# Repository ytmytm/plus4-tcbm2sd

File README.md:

# TCBM2SD 
---------
### by Maciej 'YTM/Elysium' Witkowiak

CBM 1551 paddle replacement and/or mass storage using an SD card interfacing with the Commodore C16/116/Plus4 simulating a TCBM bus 1551 disk drive.

## Ecosystem

This board can also serve as the Commodore-side TCBM interface for the [Pi1551](https://github.com/ytmytm/Pi1551), a cycle-exact Commodore 1551 emulator for Raspberry Pi. It can be used with either the [Pi1551-HAT](https://github.com/ytmytm/PI1551-hat) or [Pi1551-III](https://github.com/ytmytm/PI1551-III) interface.

It is also the TCBM interface for the [1551-rePico](https://github.com/ytmytm/1551-rePico), a 1551 drive replacement that uses a real 6510T with Raspberry Pico 2 emulating the analog parts.

The [Parobek function ROM](https://github.com/ytmytm/plus4-parobek) is a useful way to populate the 32/64 KiB ROM socket. It includes the TCBM2SD boot software, so `boot.t2sd` is not needed when using that ROM.

## Detailed manuals

- [User's manual](UserManual.md)
- [Hardware assembly, firmware compilation and flashing](HardwareFirmware.md)

## Software

- Supported by [Siz's I/O library v4](https://github.com/iszell/siziolib)
- [GEOS for tcbm2sd (D64)](geos/geostcbm.d64)
- [Collection of patched disk games](games/)
- [Parobek function ROM](https://github.com/ytmytm/plus4-parobek)
<!-- XXX patched cartridge images: OctaBASIC, Gamecart -->

[ZIP archive of the above](https://drive.google.com/drive/folders/1UYzHO3PNRJw3JCk5QNncfK0rwXZ2pFXH?usp=drive_link)

## Media

### Commodore Users Europe presentation

<a href="https://www.youtube.com/watch?v=iNGW5h6bXoA" target="_blank">
 
 <p><small>Click for video</small></p>
</a>

### Photos

*The photos and PCB view below show an older board revision and are provided for reference only.*

### Basic operations

<a href="https://www.youtube.com/watch?v=6DOctO64GS4" target="_blank">
 
 <p><small>Click for video</small></p>
</a>

### Fastloader

<a href="https://www.youtube.com/watch?v=Cf42Z9H2JiA" target="_blank">
 
 <p><small>Click for video</small></p>
</a>

## Features

### Drive simulator

TCBM2SD does not emulate a 1551, but simulates its behavior:

- DLOAD and DSAVE support for files
- read-only support for disk images (D64, D71, D81, D80, D82) as subdirectories
- standard Kernal transfer at about 3100 b/s (a little less than JiffyDOS 1541, and about twice as fast as a 1551 at 1600 b/s); fastload at about 9300 b/s (**23×** as fast as a 1541, about **6×** as fast as a 1551), with [patched Directory Browser v1.2](loader/); on par with DolphinDOS
- fastload booter embedded in the flash, available as the `*` file, which loads and runs `BOOT.T2SD` from the root directory; this can be any file that runs from BASIC. [Directory Browser patched with fastload protocol](loader/db12b.prg) is recommended. When using the Parobek function ROM, `BOOT.T2SD` is already included in the ROM and is not needed on the SD card.
- CBM DOS disk commands: `CD`, `R`, `S`, `MD`, `RD`, `I`, `UI`, `UJ`
- utility commands similar to 1571/81 BURST for fastloader, block-read/write and device number change
- device number stored permanently in EEPROM or configurable with jumpers
- support for absolute paths (up to 71 characters)
- support for SD change detection (if the SD card socket supports it) to automatically initialize card
- PREV/NEXT buttons to switch between disk images
- socket for a 32/64 KiB cartridge ROM

### Paddle replacement

It has been confirmed that tcbm2sd works as a 1551 paddle cartridge replacement with a real 1551 drive. The Arduino can be removed or disabled for this purpose.

- PLA 251641-3 and 6523T (28 pin triport) integrated into a single CPLD
- low part count: CPLD, 3.3V voltage regulator and four capacitors
- only 8 I/O addresses are needed for I/O, but certain fastloaders require the mirrored registers to be present, so we keep using whole 32-byte space like the original PLA:
  - FEE0-FEFF (instead of FEF0-FEF7) for device 8
  - FEC0-FEDF (instead of FEC0-FEC7) for device 9

### Platform for TCBM developments

The paddle part exposes all TCBM bus signals and can be used as a basis for other TCBM hardware projects.

For development, another daughterboard or a ready-to-use microcontroller module can be used. All TCBM bus signals are exposed at the cartridge edge (TCBM connector) or Arduino footprint. Signals are already at 3.3 V logic, so no additional level shifter is necessary for a Raspberry Pi.

*Please note that if a TCBM cable is connected then both pins 1 and 16 of the TCBM connection must be connected to GND. It's used by Arduino to detect if TCBM cable is attached so that Arduino can disable itself.*

### Availability

The information published here includes everything required to manufacture the PCB (Gerber files) and program the firmware.

If you want a completed unit, please drop me a message (you will find my email address at the top of [loader/loader.asm](loader/loader.asm)). I might have some units to sell; please include your country.

<!--
You can also order the hardware from PCBWay. This is the PCB only; it still requires programming the CPLD and soldering the Arduino Pro Mini (or TCBM connector) and voltage regulator:

  -->

## Case

You might also be interested in a cartridge case. It should [fit inside this one](https://www.thingiverse.com/thing:6309306), although it requires cutting a slot for the SD card.

*This example shows revision 1.1 without NEXT/PREV buttons*

There is also an [updated case project](https://www.thingiverse.com/thing:7314711) that should fit revision 1.3 and 1.4 PCBs without any extra holes.

## Credits

This project builds on work and documentation provided by others:

- [Fake6523](https://github.com/go4retro/Fake6523) and [Fake6523 HW](https://github.com/ZXByteman/Fake6523), which provided the basis for the trimmed-down 6523T implementation
- [cia-verilog](https://github.com/niklasekstrom/cia-verilog/blob/master/cia.v) which showed me a better way of interfacing with CPU bus
- [Commodore TCBM bus and protocol description](https://www.pagetable.com/?p=1324)
- [c264-magic-cart](https://github.com/msolajic/c264-magic-cart) and [C264Cart](https://github.com/hackup/C264Cart) which were my template for PCB dimensions
- [LittleSixteen](https://github.com/SukkoPera/LittleSixteen) where I found KiCad expansion port footprint and symbol, also helped me to understand how Plus/4 expansion port works
- [kicad-lib-arduino](https://github.com/g200kg/kicad-lib-arduino)
- @eper973 for Directory Browser source code
- Per Olofsson for `diskimage.c` D64/71/81 handling code

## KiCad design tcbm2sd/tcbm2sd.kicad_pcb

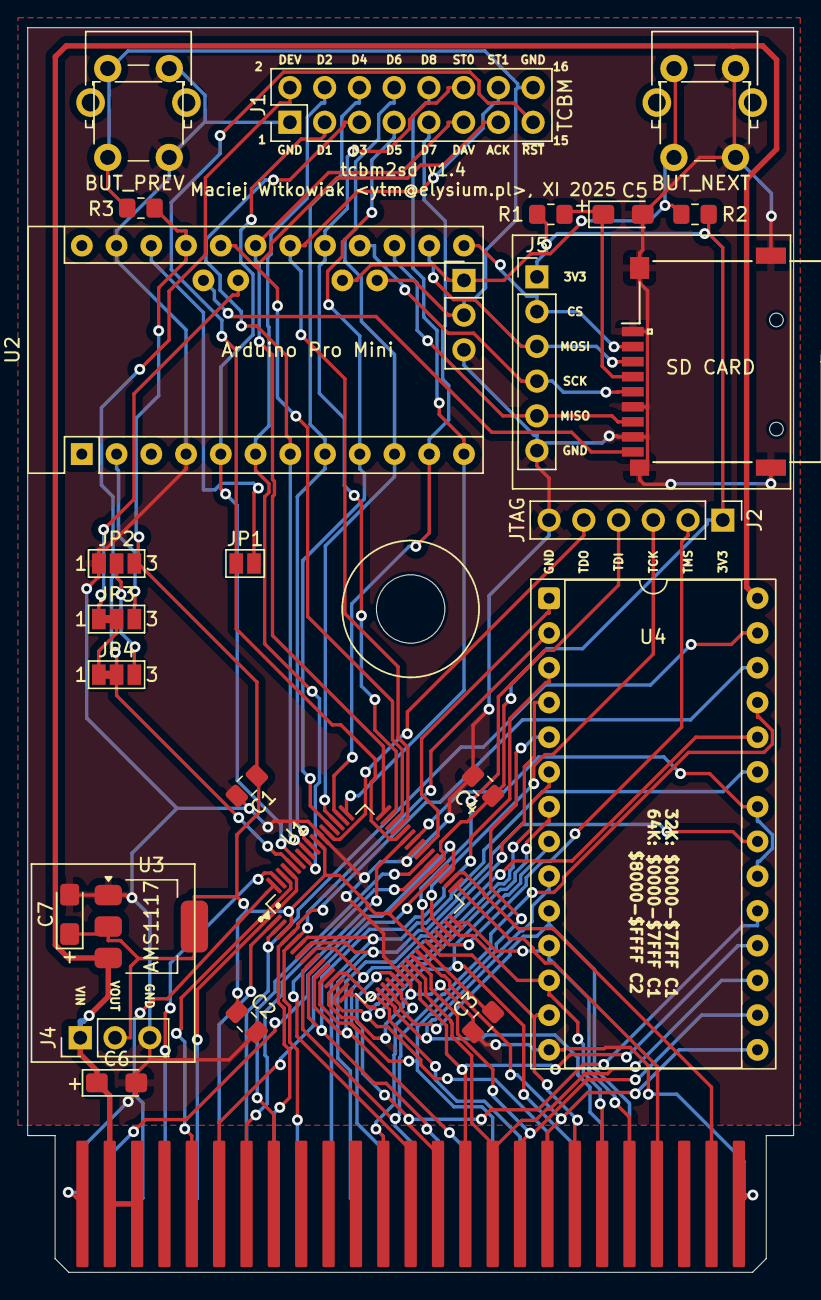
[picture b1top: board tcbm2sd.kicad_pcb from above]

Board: 2 copper layers, 56.0 x 91.0 mm, 27 parts (0 on the bottom side), 72 nets.

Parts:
C1, C2, C3, C4: 0.1uF; C_0805_2012Metric_Pad1.18x1.45mm_HandSolder
C5, C6, C7: 10µ; CP_EIA-3216-12_Kemet-S_HandSolder
J1: TCBM; PinHeader_2x08_P2.54mm_Vertical
J2: JTAG; PinHeader_1x06_P2.54mm_Vertical
J4: AMS1117; PinHeader_1x03_P2.54mm_Vertical
J5: SD CARD; PinHeader_1x06_P2.54mm_Vertical
J7: ALT_A6_A7; PinHeader_1x03_P2.54mm_Vertical
JP1: SolderJumper_2_Open; SolderJumper-2_P1.3mm_Open_Pad1.0x1.5mm
JP2: SolderJumper_3_Open; SolderJumper-3_P1.3mm_Open_Pad1.0x1.5mm_NumberLabels
JP3, JP4: SolderJumper_3_Bridged12; SolderJumper-3_P1.3mm_Bridged12_Pad1.0x1.5mm_NumberLabels
R1: 2.2R; R_0805_2012Metric_Pad1.20x1.40mm_HandSolder
R2, R3: 10K; R_0805_2012Metric_Pad1.20x1.40mm_HandSolder
SW1: BUT_PREV; SW_PUSH_6mm_OR_SW_Tactile_SPST_Angled_PTS645Vx58-2LFS
SW2: BUT_NEXT; SW_PUSH_6mm_OR_SW_Tactile_SPST_Angled_PTS645Vx58-2LFS
U1: XC9572XL-VQ64; TQFP-64_10x10mm_P0.5mm
U2: Arduino Pro Mini; Arduino_Pro_Mini
U3: AMS1117-3.3; SOT-223-3_TabPin2
U4: 27C512; DIP-28_W15.24mm_Socket
U$1: C16_CARTRIDGE; C16_CART
XS1: SD connector; Conn_uSDcard

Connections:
+3V3: C1.1, C2.1, C3.1, C4.1, C7.1, J2.1, J4.2, J5.1, JP2.3 (B), R1.2, R2.1, R3.1, U1.3 (VCC), U1.26 (VCCIO), U1.37 (VCC), U1.55 (VCCIO), U2.21 (VCC), U3.2 (VO)
/A0: U1.18, U4.10 (A0), U$1.Y (A0)
/A1: U1.17 (I/O/GCK3), U4.9 (A1), U$1.X (A1)
/A2: U1.16 (I/O/GCK2), U4.8 (A2), U$1.W (A2)
/A3: U1.15 (I/O/GCK1), U4.7 (A3), U$1.V (A3)
/A4: U1.13, U4.6 (A4), U$1.U (A4)
/A5: U1.12, U4.5 (A5), U$1.T (A5)
/A6: U1.11, U4.4 (A6), U$1.S (A6)
/A7: U1.10, U4.3 (A7), U$1.R (A7)
/A8: U1.9, U4.25 (A8), U$1.P (A8)
/A9: U1.8, U4.24 (A9), U$1.N (A9)
/A10: U1.7, U4.21 (A10), U$1.M (A10)
/A11: U1.6, U4.23 (A11), U$1.L (A11)
/A12: U1.5 (I/O/GTS1), U4.2 (A12), U$1.K (A12)
/A13: U1.4, U4.26 (A13), U$1.J (A13)
/A14: U1.2 (I/O/GTS2), U4.27 (A14), U$1.H (A14)
/A15: U1.1, U$1.F (A15)
/ACK: J1.13, U1.46, U2.20 (D17/A3)
/AEC: U1.33, U$1.22 (AEC)
/ALT_A6: J1.16, J7.2, R3.2, SW1.1, U2.A6
/ALT_A7: J7.1, R2.2, SW2.1, U2.A7
/BA: U1.43, U$1.13 (BA)
/C1HI: U1.36, U$1.6 (C1HI)
/C1LO: U1.35, U$1.B (C1LO)
/C2HI: U1.39, U$1.8 (C2HI)
/C2LO: U1.38, U$1.7 (C2LO)
/D0: U1.32, U4.11 (D0), U$1.21 (D0)
/D1: U1.31, U4.12 (D1), U$1.20 (D1)
/D2: U1.27, U4.13 (D2), U$1.19 (D2)
/D3: U1.25, U4.15 (D3), U$1.18 (D3)
/D4: U1.24, U4.16 (D4), U$1.17 (D4)
/D5: U1.23, U4.17 (D5), U$1.16 (D5)
/D6: U1.22, U4.18 (D6), U$1.15 (D6)
/D7: U1.20, U4.19 (D7), U$1.14 (D7)
/DAV: J1.11, U1.48, U2.19 (D16/A2)
/DEV: J1.2, JP4.2 (C), U1.60
/DIO1: J1.3, U1.59, U2.5 (D2)
/DIO2: J1.4, U1.58, U2.6 (~D3)
/DIO3: J1.5, U1.57, U2.7 (D4)
/DIO4: J1.6, U1.56, U2.8 (~D5)
/DIO5: J1.7, U1.52, U2.9 (~D6)
/DIO6: J1.8, U1.51, U2.10 (D7)
/DIO7: J1.9, U1.50, U2.11 (D8)
/DIO8: J1.10, U1.49, U2.12 (~D9)
/MUX: U1.19, U$1.12 (MUX)
/PHI0: U1.61, U$1.E (PHI0)
/PHI2: U1.34, U$1.24 (PHI2)
/ROM_A15: U1.40, U4.1 (A15)
/R/~W: U1.62, U$1.5 (R/~W)
/SD_CD: U2.A5, XS1.9 (CD)
/SD_CS: J5.2, U2.13 (~D10), XS1.2 (CS/DAT3)
/SD_MISO: J5.5, U2.15 (D12), XS1.7 (DO/DAT0)
/SD_MOSI: J5.3, U2.14 (~D11), XS1.3 (DI/CMD)
/SD_SCK: J5.4, U2.16 (D13), XS1.5 (CLK)
/STATUS0: J1.12, U1.47, U2.17 (D14/A0)
/STATUS1: J1.14, U1.45, U2.18 (D15/A1)
/TCK: J2.3, U1.30 (TCK)
/TDI: J2.4, U1.28 (TDI)
/TDO: J2.5, U1.53 (TDO)
/TMS: J2.2, U1.29 (TMS)
/VCC: C6.1, J4.1, U3.3 (VI), U4.28 (VCC), U$1.2 (5V), U$1.3 (5V)
/~RAS: U1.63, U$1.D (~RAS)
/~RESET_3_3V: J1.15, JP1.1 (A), U1.44
/~RESET: U1.64 (I/O/GSR), U$1.C (~RESET)
/~ROMCS: U1.42, U4.20 (~CE), U4.22 (~OE)
GND: C1.2, C2.2, C3.2, C4.2, C5.2, C6.2, C7.2, J1.1, J2.6, J4.3, J5.6, J7.3, JP2.1 (A), SW1.2, SW2.2, U1.14 (GND), U1.21 (GND), U1.41 (GND), U1.54 (GND), U2.4 (GND), U2.23 (GND), U3.1 (GND), U4.14 (GND), U$1.1 (GND), U$1.25 (GND), U$1.A (GND), U$1.CC (GND), XS1.1 (DAT2), XS1.6 (GND), XS1.8 (DAT1)
unnamed: JP1.2 (B), U2.22 (RST)
unnamed: JP2.2 (C), JP4.3 (B)
unnamed: JP3.1 (A), U2.A4
unnamed: JP3.3 (B), U2.2 (D0/RX)
unnamed: JP3.2 (C), JP4.1 (A)
unnamed: C5.1, R1.1, XS1.4 (Vdd)

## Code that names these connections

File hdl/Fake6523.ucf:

# Fake6523A-28
NET "_reset"		LOC = "P64"  ; # /RESET exp. C
NET "_write"		LOC = "P62"  ; # R/W exp. 5
NET "data<0>"		LOC = "P32"  ; # D0 exp. 21
NET "data<1>"		LOC = "P31"  ; # D1 exp. 20
NET "data<2>"		LOC = "P27"  ; # D2 exp. 19
NET "data<3>"		LOC = "P25"  ; # D3 exp. 18
NET "data<4>"		LOC = "P24"  ; # D4 exp. 17
NET "data<5>"		LOC = "P23"  ; # D5 exp. 16
NET "data<6>"		LOC = "P22"  ; # D6 exp. 15
NET "data<7>"		LOC = "P20"  ; # D7 exp. 14
NET "port_a<0>"	LOC = "P59"  ; # DIO1, <-> wire 3
NET "port_a<1>"	LOC = "P58"  ; # DIO2, <-> wire 4
NET "port_a<2>"	LOC = "P57"  ; # DIO3, <-> wire 5
NET "port_a<3>"	LOC = "P56"  ; # DIO4, <-> wire 6
NET "port_a<4>"	LOC = "P52"  ; # DIO5, <-> wire 7
NET "port_a<5>"	LOC = "P51"  ; # DIO6, <-> wire 8
NET "port_a<6>"	LOC = "P50"  ; # DIO7, <-> wire 9
NET "port_a<7>"	LOC = "P49"  ; # DIO8, <-> wire 10
NET "port_b<0>"	LOC = "P47"  ; # STATUS0, <-, wire 12
NET "port_b<1>"	LOC = "P45"  ; # STATUS1, <-, wire 14
NET "port_c<6>"	LOC = "P46"  ; # ACK, ->, wire 13 (controller's ACK out, drive's DAV in)
NET "port_c<7>"	LOC = "P48"  ; # DAV, <-, wire 11 (controller's DAV in,  drive's ACK out)
NET "rs<0>"			LOC = "P18"  ; # A0 exp. Y
NET "rs<1>"			LOC = "P17"  ; # A1 exp. X
NET "rs<2>"			LOC = "P16"  ; # A2 exp. W
# /CS from PLA (18) F0

# PLA outputs
#NET "_cs"			LOC = "P34"  ;	# PLA F0 (18) -> 6523 /CS (12)
#NET "pla_f7" 		LOC = "P33"  ; # PLA F7 (10) -> I0 (2)
NET "phi2"			LOC = "P34"  ;	# Phi2 exp. 24
NET "aec" 		LOC = "P33"  ; # AEC exp. 22
NET "_cas"		LOC = "P42"  ; # /CAS exp. 11
NET "ba"		LOC = "P43"  ; # BA exp. 13
# PLA inputs
# PLA I0 (9) <- PLA F7 (10) (wired back)
NET "pla_i<1>"		LOC = "P6"	 ; # PLA I1 (8)   <- A11 exp. L
NET "pla_i<2>"		LOC = "P5"	 ; # PLA I2 (7)   <- A12 exp. K
NET "pla_i<3>"    LOC = "P4"	 ; # PLA I3 (6)   <- A13 exp. J
NET "pla_i<4>"		LOC = "P2"	 ; # PLA I4 (5)   <- A14 exp. H
NET "pla_i<5>"		LOC = "P1"	 ; # PLA I5 (4)   <- A15 exp. F
NET "pla_i<6>"		LOC = "P61"  ; # PLA I6 (3)   <- Phi0 exp. E
NET "pla_i<7>"		LOC = "P63"	 ; # PLA I7 (2)   <- /RAS exp. D
NET "pla_i<8>"		LOC = "P60"  ; # PLA I8 (27)  <- DEV signal from device (0 or 1), wire 2
NET "pla_i<9>"    LOC = "P7"   ; # PLA I9 (26)  <- A10 exp. M
NET "pla_i<10>"   LOC = "P19"  ; # PLA I10 (25) <- MUX exp. 12
NET "pla_i<11>"   LOC = "P8"   ; # PLA I11 (24) <- A9 exp. N
NET "pla_i<12>"   LOC = "P9"   ; # PLA I12 (23) <- A8 exp. P
NET "pla_i<13>"   LOC = "P10"  ; # PLA I13 (22) <- A7 exp. R
NET "pla_i<14>"   LOC = "P11"  ; # PLA I14 (21) <- A6 exp. S
NET "pla_i<15>"   LOC = "P12"  ; # PLA I15 (20) <- A5 exp. T
# additional inputs
NET "addr<4>"     LOC = "P13"  ; # PLA xxx      <- A4 exp. U
NET "addr<3>"     LOC = "P15"  ; # PLA xxx      <- A3 exp. V
# additional output
NET "_resetout"   LOC = "P44"  ; # copy 5V /RESET to 3.3V /RESET

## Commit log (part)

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2024-07-05 handle file saving to SD card
2024-07-05 dummy directory load
2024-07-05 remark about file pattern matching
2024-07-06 real directory listing
2024-07-06 keep current path in 'pwd' string (must end with '/')
2024-07-06 improve drive status message handling
2024-07-06 keep SD code enabled at all times now
2024-07-06 in blocking read command function wait only for a valid command
2024-07-07 add volatile inline clauses to all low level h/w functions
2024-07-07 disable debug
2024-07-07 show current directory name as volume label
2024-07-07 some programs will expect that command is executed right after UNLISTEN, not after following CLOSE (which may not come at all - Directory Browser)
2024-07-07 try to handle transfer problems within filebrowser/directory browser with a tiny delay (but port_read_slow is very slow)
2024-07-08 logic with feedback, seems to fix hangup problems
2024-07-08 clarify DAV/ACK confusion
2024-07-08 correct TCBM 0/1 IEC 8/9 numbering info (A5==1 is for device 8)
2024-07-08 comments
2024-07-08 updated logic: use A4/A3 to decode addresses, no more glitches, copy /RESET in 3.3V to pin 44
2024-07-08 updated after latest runs
2024-07-08 DEV must be an output, it can't be an input from CPLD because Arduino won't have time to react (it would come from A4/A5 address lines)
2024-07-09 remove dead code
2024-07-09 convert everything to lowercase PETSCII (uppercase ASCII)
2024-07-09 don't prepend with current dir (pwd) if filename starts with '/'
2024-07-09 move state_init to reset input buffer
2024-07-09 be sure to close opened files
2024-07-09 credits
2024-07-09 return so that valid U0>x results in OK status
2024-07-09 fix comments about pin definitions
2024-07-10 remove delay, it's no longer necessary
2024-07-10 use plain ASCII for directory listing (same as with filename matching)
2024-07-10 put all Serial debug messages within 'if debug {}'; gcc optimizes this away and it's cleaner than #ifdef DEBUG
2024-07-10 PCB top view
2024-07-10 added README placeholder
2024-07-12 directory browser v1.2 patched for fastloader; first with loader part disassembled no changes yet; this is binary identical
2024-07-12 gitignore
2024-07-12 comments and assert
2024-07-13 WIP fastload protocol and directory browser patch
2024-07-14 when asked for '*' load embedded Directory Browser 1.2 (works with shift+run/stop)
2024-07-14 disable browser when debug is enabled (would not fit in flash)
2024-07-14 do nothing with empty command
2024-07-14 support for rename command
2024-07-14 document new disk commands
2024-07-15 extra documentation
2024-07-17 diary added
2024-07-21 comments and indentation
2024-07-21 it's more readable to send out whole strings
2024-07-21 report 9999 blocks free (no need for a real value)
2024-07-21 missing cases for STATE_BROWSER (STATE_STAT and STATE_BROWSER are handled in the same way)
2024-07-21 correct comment
2024-07-21 fastload protocol for directory with test program
2024-07-21 SHIFT+RUN/STOP to load tiny loader that will find and load 'BOOT.T2SD' with fastload protocol
2024-07-21 increase name buffer size to 256 bytes as dictated by SdFat
2024-07-21 if filename is longer than 16 characters, fall back on 8.3 short DOS filename
2024-07-21 map 0x7e ~ (short filename marker) to 0x5e <- and back, because otherwise it came out as (pi) and short filename couldn't be found
2024-07-21 reformat and indents
2024-07-21 reset if BOOT.T2SD file not found
2024-07-21 correct DISABLE_BROWSER option (not relevant anymore)
2024-07-23 clean pcb, new revision
2024-07-23 - solder jumpers to choose DEV from +33V/GND/A4/D1 - TCBM connector - removed debug pads - RESET 3.3V, through solder jumper - cut connection to Arduino pin 3 (RP2040 clone has GND there) - VCC net c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
2024-07-24 new plots: schematic and gerber files
2024-07-24 jlcpcb manufacturing files: BOM and placement (corrected U1 rotation from 45 to -45)
2024-07-24 updated snapshot
2024-07-24 correctly skip partition number (skip '0' only if the next character is ':')
2024-07-24 #define for maximum size of file's long name
2024-07-24 remove all arduino strings
2024-07-25 diskimage 0.95 library converted to readonly+SdFat interface ; http://web.archive.org/web/20240330040552/https://www.paradroid.net/diskimage/
2024-07-25 enter/exit disk images; list disk image contents
2024-07-25 put filetype strings in flash
2024-07-25 reuse input_buf for temporary storage for directory file entry buffer
2024-07-25 reduce input/output buffer size
2024-07-25 cleanup compiler warnings
2024-07-25 bump minor version by 1 because we support disk images now
2024-07-25 update on RAM situation: needs about 600 free bytes left for dynamic stuff, PATH_SIZE is used twice, use 24 for debug, safe max is about 72 now
2024-07-26 reset status to 00 (b/c output_buf is altered by match_filename)
2024-07-27 directory browser 1.2 (tcbm) binary and code samples
2024-07-27 recognize D71/81 with error info and D64 with 40 and 42 tracks (read only, BAM not correctly handled for 40/42 even for free blocks)
2024-07-27 correct directory search for D81
2024-07-27 case info
2024-07-27 dimensions
2024-08-04 fix compiler warning
2024-08-15 updated to rev1.1
2024-08-18 make all unused port bits hi-z
2024-08-25 drop PLA outputs, use more exp. port inputs to CPLD (just in case) own SMD 3.3V regulator circuit own SD card circuit (SD card model etc.) from SD2IEC plug https://www.hackup.net/2018/10/sd2iecplug-v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
2024-08-30 add 32/64K EEPROM with /CS done using two diodes with pullup as AND one more pullup for A15 line connector for remaining Arduino lines with GND connection to short it to disable Arduino on boot
2024-09-03 twin dip/soic footprints (won't use them)
2024-09-03 production files
2024-09-04 cleanup pins, pla_f7/_cs debug outputs back - to gpio pins
2024-09-07 enable pullups on DIO1-8
2024-09-07 disable Arduino if BUT_PREV is tied to GND
2024-09-07 load and save on any channel except 15
2024-09-11 alternative A7 pullup, but disabling function disabled for now
2024-09-12 A6/A7 are analog-only, can't use as digital inputs
2024-09-14 simplified design that actually works on both 7501 and 6510
2024-09-14 back up Fake6523 name
2024-09-14 diary
2024-09-14 urls for reference
2024-09-15 save one byte
2024-09-15 call CLOSE after CLKCHN so that UNTALK is properly sent
2024-09-15 use Kernal jumptable for function calls; call UNTALK at the end (not required)
2024-09-15 if in image, then '*' loads first file, not browser booter
2024-09-15 handle special case for directory listing with JiffyDOS @$ - calls UNTALK/TALK/TKSA after each received line
2024-09-15 handle PREV/NEXT buttons; a bit clumsy because we need to scan directory each time
2024-09-16 A6/A7 might not be connected (pulled up) at all, check that by probing A7 first - if it's not pulled up we can't use these buttons (or TCBM cable sense) at all
2024-09-16 standardload / fastload refactor - merge procedures into one to save flash space
2024-09-16 restore analog threshold
2024-09-16 reduce debouncing delay for prev/next buttons
2024-09-16 if going to previous image of the first image or next image of the last image - stay on the current image
2024-09-16 if SD card was changed close the image, but also go to root folder (reload_sd_card() won't do that because it's called by I/UI/UJ commands)
2024-09-17 smaller simpler loader with quasi-BURST CMD TEN command (fastload utility); bump version to indicate utility U0 commands are present https://www.devili.iki.fi/Computers/Commodore/C1571/firmware/fastu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
2024-09-17 utility command U0<$3F><track><sector> to load file from disk image by its first block's t&s
2024-09-18 public function to compute offset to given track&sector within the image file
2024-09-18 now we support block-write, so disk image has to be opened in O_RDWR mode
2024-09-18 block-read/write utility commands and new state data streaming function
2024-09-18 simple example about utility commands for block-read/write
2024-09-18 update about block-read/write
2024-09-19 save one RAM byte, global cbm_errno is not used
2024-09-19 docs update
2024-09-19 corrected
2024-09-25 less verbose debug2
2024-09-25 no need to wait for anything with fastprotocol - the last byte was already confirmed, just cleanup
2024-09-25 GEOS support
2024-09-26 add debug2 or debug2>1 to more cases
2024-09-26 correct finish of fast block read/write
2024-09-26 clean bootdisk, without TDISK 1551 drive code file, to have 3 more free blocks
2024-09-28 cleanup and credits
2024-09-29 copy only low level from /RESET line, keep /RESET_3_3V high impedance otherwise
2024-10-01 handle ROM in CPLD; temporarily disable resetout and reuse it for rom_cs (in the next rev. use loc P42 instead and bring back resetout)
2024-10-01 remove GPIO connector, 74'00, diodes and pullup; added pullups for A6/A7; JP1 (reset passthrough) default open; bump revision to 1.3
2024-10-04 updated routing
2024-10-06 dual footprint for pushbutton switch straight or angled
2024-10-09 confirmed working on my C16
2024-10-13 option to disable A6/A7 buttons for v1.0/v1.1 PCBs
2024-10-17 scan 20 files each way for previous/next button
2024-10-17 backport from rev 1.3, c90f487 ("simplified design that actually works on both 7501 and 6510", 2024-09-14)
2024-10-17 backport from rev 1.3 but with A6/A7 buttons disabled by default: DISABLE_NEXT_PREV_BUT (you need pullups to 3.3V to make them work)
2024-10-17 release files for revision 1.3
2024-10-19 call RESTOR to disable any hooks installed by a cartridge (e.g. TURBO PLUS)
2024-10-28 support for D80/D82 disk images and small optimizations in diskimage; #4
2024-11-07 Giana Sisters patched for TCBM protocol and TCBM fastload ; https://plus4world.powweb.com/software/Giana_Sisters
2024-11-07 Alpharay patched for TCBM protocol and TCBM fastload ; https://plus4world.powweb.com/software/Alpharay
2024-11-07 alpharay disk image for download
2024-11-10 added patched Pets Rescue (IEC) ; https://plus4world.powweb.com/software/Pets_Rescue
2024-11-11 added patched Prince of Persia ; https://plus4world.powweb.com/software/Prince_of_Persia
2024-11-11 added patched Turbo Outrun ; https://plus4world.powweb.com/software/Turbo_Outrun
2024-11-14 Lykia Prologue from https://plus4world.powweb.com/software/Lykia
2024-11-15 correct range; map $5F to $7E in 2nd filename character because TCBM2SD 00,02 does this...
2024-11-17 Lykia patched for TCBM2SD ; SD2IEC version from https://plus4world.powweb.com/software/Lykia (Final version)
2024-11-29 added patched Bards Tale 3 ; https://plus4world.powweb.com/software/Bards_Tale_III (Csory)
2024-11-30 restore text color palette at bash113 in case it gets corrupted by something
2024-11-30 user's manual
2024-12-01 restructured documentation
2024-12-01 autogenerated TOC
2024-12-12 Link to SD card contents
2025-04-09 export 3D PCB model to make it easier for case designers
2025-04-09 presentation used for https://www.youtube.com/watch?v=iNGW5h6bXoA
2025-07-27 there is IRQ handler too
2025-07-27 repack attempt
2025-07-27 docs updates, UTIL incorporated into binary
2025-07-27 repack version copied as src, renamed
2025-07-27 TCBM2SD fast block read/write, adapted from Bard's Tale patch, spread over empty places, but Exomizer can't decrunch this directly
2025-07-28 assertions
2025-07-28 rewrite high part of the loader with .pseudopc ; reenable exomizer
2025-07-28 boot3.bin loader ($5600-$57ff) won't be used anymore
2025-07-28 local IRQHandler so that we don't need boot3.bin anymore
2025-07-28 save some space by patching boot2.bin directly
2025-07-28 comments about disassembly info
2025-07-28 Dragon Wars docs
2025-11-08 v1.4 with correct silkscreen info about C1/C2 ROM banks and 3.3V /RESET routed to TCBM connector instead of 5V /RESET
2026-01-14 support for Ghosts'n'Goblins
2026-01-23 Ghosts'n'Goblins updated to REV2 (2026-01-19) from https://plus4world.powweb.com/software/Ghosts_N_Goblins_Arcade_Version
2026-03-18 extend I/O addresses to mirror FEC0-FEC7 in FEC0-FEDF, FEF0-FEF7 in FEE0-FEFF
